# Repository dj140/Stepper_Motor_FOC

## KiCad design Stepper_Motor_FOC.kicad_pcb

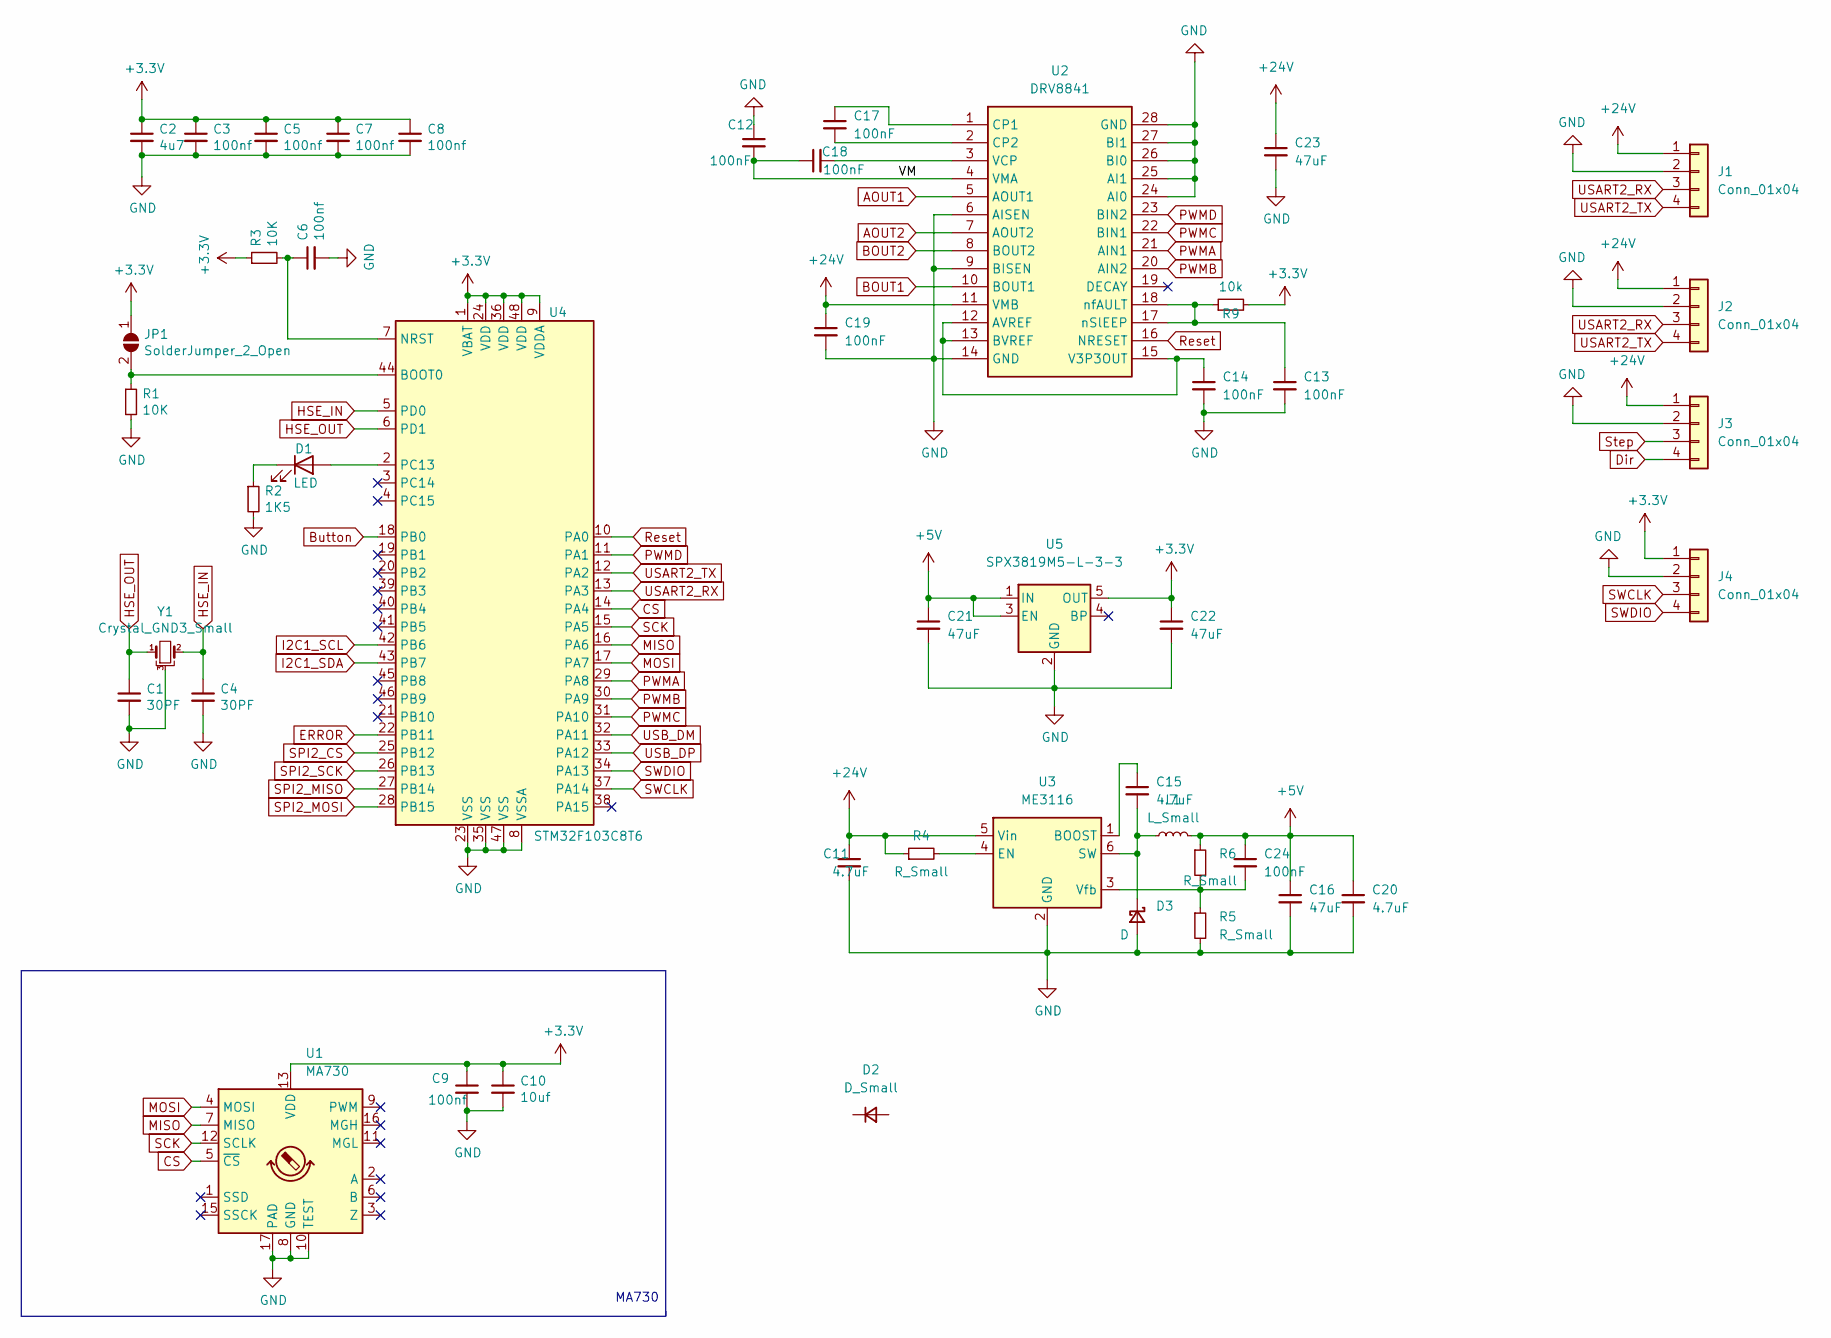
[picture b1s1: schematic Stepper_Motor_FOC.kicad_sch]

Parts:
C1, C4: 30PF; C_0402_1005Metric
C2: 4u7; C_0402_1005Metric
C3, C5, C6, C7, C8, C9: 100nf; C_0402_1005Metric
C10: 10uf; C_0402_1005Metric
C11: 4.7uF; C_1206_3216Metric_Pad1.33x1.80mm_HandSolder
C12, C13, C14, C17, C18, C19, C24: 100nF; C_0402_1005Metric_Pad0.74x0.62mm_HandSolder
C15, C20: 4.7uF; C_0402_1005Metric_Pad0.74x0.62mm_HandSolder
C16, C21, C22, C23: 47uF; C_1206_3216Metric_Pad1.33x1.80mm_HandSolder
D1: LED; LED_0402_1005Metric
D2: D_Small
D3: D
J1, J2, J3: Conn_01x04; JST_EH_S4B-EH_1x04_P2.50mm_Horizontal
J4: Conn_01x04; Molex_PicoBlade_53048-0410_1x04_P1.25mm_Horizontal
JP1: SolderJumper_2_Open; SoldJumper-2-P0.5mm_Open_RoundedPad
L1: L_Small; L_0420
R1, R3: 10K; R_0402_1005Metric
R2: 1K5; R_0402_1005Metric
R4, R5, R6: R_Small; C_0402_1005Metric_Pad0.74x0.62mm_HandSolder
R9: 10k; C_0402_1005Metric_Pad0.74x0.62mm_HandSolder
U1: MA730; QFN-16-1EP_3x3mm_P0.5mm_EP1.75x1.75mm
U2: DRV8841; IC_TPS61196PWPRQ1
U3: ME3116; SOT-23-6
U4: STM32F103C8T6; LQFP-48_7x7mm_P0.5mm
U5: SPX3819M5-L-3-3; SOT-23-5
Y1: Crystal_GND3_Small; OSC_CSTCE8M00G55-R0

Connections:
+3V3: C2.1, C3.1, C5.1, C7.1, C8.1, C9.1, C10.1, C22.1, J4.1, JP1.1 (A), R3.1, R9.2, U1.13 (VDD), U4.1 (VBAT), U4.9 (VDDA), U4.24 (VDD), U4.36 (VDD), U4.48 (VDD), U5.5 (OUT)
+5V: C16.1, C20.1, C21.1, C24.1, L1.2, R6.1, U5.1 (IN), U5.3 (EN)
+24V: C11.1, J1.1, J2.1, J3.1, R4.1, U3.5 (Vin)
AOUT1: U2.5 (AOUT1)
AOUT2: U2.7 (AOUT2)
BOUT1: U2.10 (BOUT1)
BOUT2: U2.8 (BOUT2)
Button: U4.18 (PB0)
CS: U1.5 (~CS), U4.14 (PA4)
Dir: J3.4
ERROR: U4.22 (PB11)
GND: C1.2, C2.2, C3.2, C4.2, C5.2, C6.2, C7.2, C8.2, C9.2, C10.2, C11.2, C12.1, C13.2, C14.2, C16.2, C19.2, C20.2, C21.2, C22.2, C23.2, D3.2 (A), J1.2, J2.2, J3.2, J4.2, R1.2, R2.2, R5.2, U1.8 (GND), U1.10 (TEST), U1.17 (PAD), U2.6 (AISEN), U2.9 (BISEN), U2.14 (GND), U2.24 (AI0), U2.25 (AI1), U2.26 (BI0), U2.27 (BI1), U2.28 (GND), U3.2 (GND), U4.8 (VSSA), U4.23 (VSS), U4.35 (VSS), U4.47 (VSS), U5.2 (GND), Y1.3
HSE_IN: C4.1, U4.5 (PD0), Y1.2
HSE_OUT: C1.1, U4.6 (PD1), Y1.1
I2C1_SCL: U4.42 (PB6)
I2C1_SDA: U4.43 (PB7)
MISO: U1.7 (MISO), U4.16 (PA6)
MOSI: U1.4 (MOSI), U4.17 (PA7)
unnamed: C6.1, R3.2, U4.7 (NRST)
unnamed: C14.1, U2.12 (AVREF), U2.13 (BVREF), U2.15 (V3P3OUT)
unnamed: C17.1, U2.1 (CP1)
unnamed: C17.2, U2.2 (CP2)
unnamed: D1.1 (K), R2.1
unnamed: D1.2 (A), U4.2 (PC13)
unnamed: JP1.2 (B), R1.1, U4.44 (BOOT0)
unnamed: R4.2, U3.4 (EN)
unnamed: C24.2, R5.1, R6.2, U3.3 (Vfb)
unnamed: C13.1, R9.1, U2.17 (nSlEEP), U2.18 (nfAULT)
unnamed: C18.2, U2.3 (VCP)
unnamed: C15.1, U3.1 (BOOST)
unnamed: C15.2, D3.1 (K), L1.1, U3.6 (SW)
PWMA: U2.21 (AIN1), U4.29 (PA8)
PWMB: U2.20 (AIN2), U4.30 (PA9)
PWMC: U2.22 (BIN1), U4.31 (PA10)
PWMD: U2.23 (BIN2), U4.11 (PA1)
Reset: U2.16 (NRESET), U4.10 (PA0)
SCK: U1.12 (SCLK), U4.15 (PA5)
SPI2_CS: U4.25 (PB12)
SPI2_MISO: U4.27 (PB14)
SPI2_MOSI: U4.28 (PB15)
SPI2_SCK: U4.26 (PB13)
SWCLK: J4.3, U4.37 (PA14)
SWDIO: J4.4, U4.34 (PA13)
Step: J3.3
USART2_RX: J1.3, J2.3, U4.13 (PA3)
USART2_TX: J1.4, J2.4, U4.12 (PA2)
USB_DM: U4.32 (PA11)
USB_DP: U4.33 (PA12)

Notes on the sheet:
MA730

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
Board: 2 copper layers, 44 parts (1 on the bottom side), 33 nets, no tracks yet.

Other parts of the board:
R7, R8: 10k; C_0402_1005Metric_Pad0.74x0.62mm_HandSolder

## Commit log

2022-02-14 update sch
